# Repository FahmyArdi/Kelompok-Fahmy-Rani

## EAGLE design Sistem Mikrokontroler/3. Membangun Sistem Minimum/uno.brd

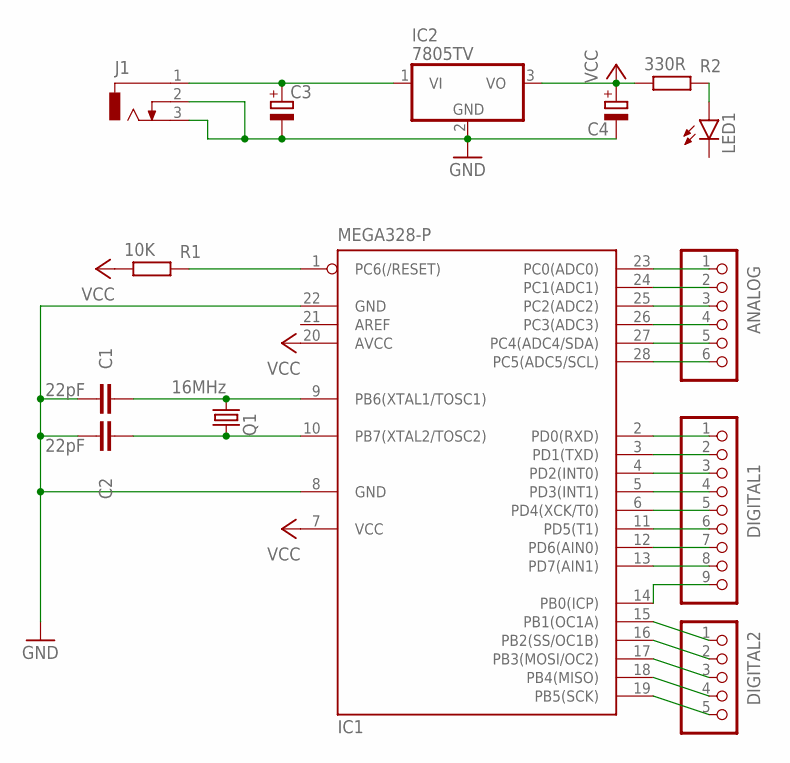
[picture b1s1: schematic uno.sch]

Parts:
ANALOG: PINHD-1X6; 1X06
C1, C2: 22pF; C025-024X044
C3, C4: CPOL-EUE2.5-6; E2,5-6
DIGITAL1: PINHD-1X9; 1X09
DIGITAL2: PINHD-1X5; 1X05
IC1: MEGA328-P; DIL28-3
IC2: 7805TV; TO220V
J1: DCJ0303
LED1: LED3MM
Q1: 16MHz; HC49U70
R1: 10K; 0207/10
R2: 330R; 0207/10

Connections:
GND: C1.1, C2.1, C3.-, C4.-, IC1.8 (GND), IC1.22 (GND), IC2.2 (GND), J1.2, J1.3
unnamed: IC1.1 (PC6(/RESET)), R1.2
unnamed: C1.2, IC1.9 (PB6(XTAL1/TOSC1)), Q1.2
unnamed: C2.2, IC1.10 (PB7(XTAL2/TOSC2)), Q1.1
unnamed: ANALOG.1, IC1.23 (PC0(ADC0))
unnamed: ANALOG.2, IC1.24 (PC1(ADC1))
unnamed: ANALOG.3, IC1.25 (PC2(ADC2))
unnamed: ANALOG.4, IC1.26 (PC3(ADC3))
unnamed: ANALOG.5, IC1.27 (PC4(ADC4/SDA))
unnamed: ANALOG.6, IC1.28 (PC5(ADC5/SCL))
unnamed: DIGITAL1.1, IC1.2 (PD0(RXD))
unnamed: DIGITAL1.2, IC1.3 (PD1(TXD))
unnamed: DIGITAL1.3, IC1.4 (PD2(INT0))
unnamed: DIGITAL1.4, IC1.5 (PD3(INT1))
unnamed: DIGITAL1.5, IC1.6 (PD4(XCK/T0))
unnamed: DIGITAL1.6, IC1.11 (PD5(T1))
unnamed: DIGITAL1.7, IC1.12 (PD6(AIN0))
unnamed: DIGITAL1.8, IC1.13 (PD7(AIN1))
unnamed: DIGITAL1.9, IC1.14 (PB0(ICP))
unnamed: DIGITAL2.1, IC1.15 (PB1(OC1A))
unnamed: DIGITAL2.2, IC1.16 (PB2(SS/OC1B))
unnamed: DIGITAL2.3, IC1.17 (PB3(MOSI/OC2))
unnamed: DIGITAL2.4, IC1.18 (PB4(MISO))
unnamed: DIGITAL2.5, IC1.19 (PB5(SCK))
unnamed: C3.+, IC2.1 (VI), J1.1
unnamed: LED1.A, R2.2
VCC: C4.+, IC1.7 (VCC), IC1.20 (AVCC), IC2.3 (VO), R1.1, R2.1

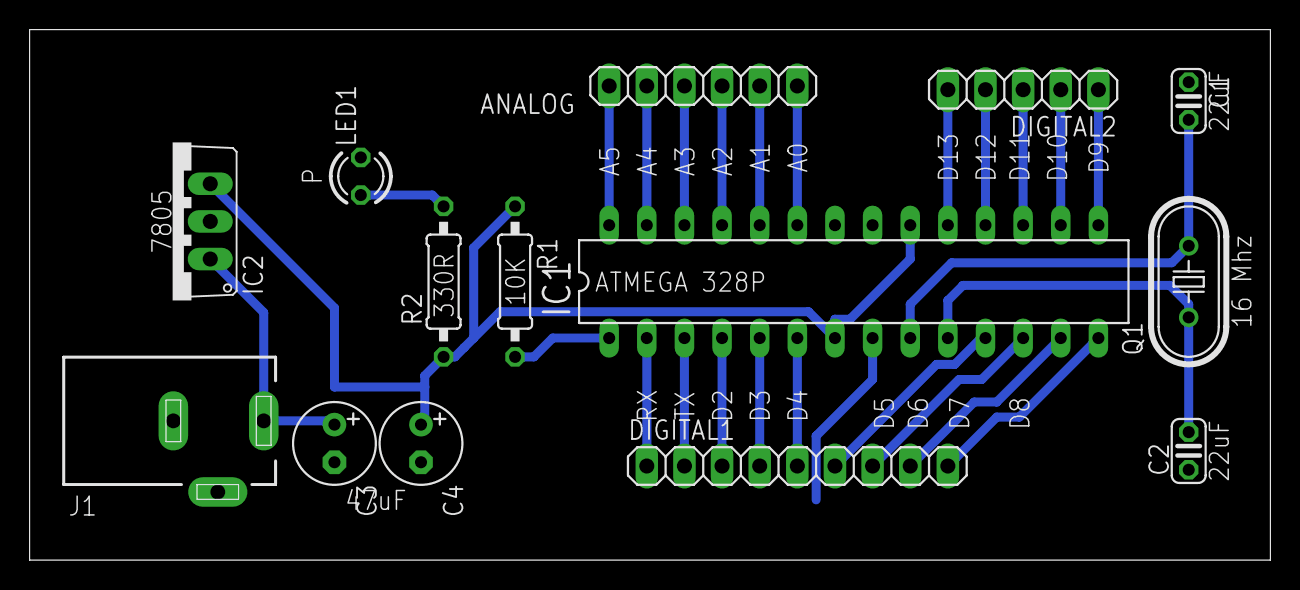
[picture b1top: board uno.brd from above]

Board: 2 copper layers, 83.7 x 35.8 mm, 14 parts (0 on the bottom side), 27 nets.

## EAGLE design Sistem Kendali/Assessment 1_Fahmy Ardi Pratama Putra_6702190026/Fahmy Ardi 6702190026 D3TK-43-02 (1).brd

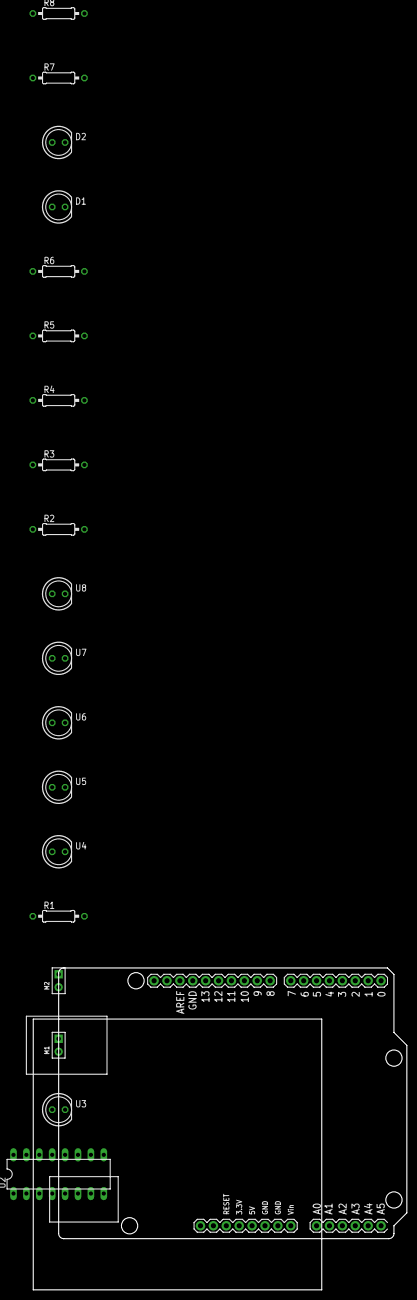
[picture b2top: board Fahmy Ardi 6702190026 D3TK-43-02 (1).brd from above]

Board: 2 copper layers, 73.6 x 63.4 mm, 20 parts (0 on the bottom side), 22 nets, no tracks yet.

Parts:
D1, D2: LED5MM
M1, M2: 2P-2.54-65/35MIL
R1, R2, R3, R4, R5, R6: 33k‎Ω; 0207/10
R7, R8: 330k‎Ω; 0207/10
U1: ARDUINO_UNO
U2: DIL16
U3, U4, U5, U6, U7, U8: LED5MM

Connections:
unnamed: R1.2, U1.A0, U3.A
unnamed: R2.2, U1.A1, U4.A
unnamed: R3.2, U1.A2, U5.A
unnamed: R4.2, U1.A3, U6.A
unnamed: R5.2, U1.A4, U7.A
unnamed: R6.2, U1.A5, U8.A
unnamed: D1.A, R7.1
unnamed: D2.K, R1.1, R2.1, R3.1, R4.1, R5.1, R6.1, U1.GND., U2.4, U2.5, U2.12, U2.13
unnamed: D2.A, R8.1
unnamed: R8.2, U1.8
unnamed: R7.2, U1.7
unnamed: U1.4, U2.1
unnamed: U1.5, U2.2
unnamed: M1.2, U2.3
unnamed: M1.1, U2.6
unnamed: U1.6, U2.7
unnamed: U1.2, U2.9
unnamed: U1.3, U2.10
unnamed: M2.2, U2.11
unnamed: M2.1, U2.14
unnamed: U1.11, U2.15
unnamed: D1.K, U1.5V, U2.8, U2.16, U4.K, U5.K, U6.K, U7.K, U8.K

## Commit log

2021-03-09 tugas sebelumnya
2021-03-10 modul 3
2021-03-22 Assigment 1 Modul 4.rar
2021-03-24 Tugas 6
2021-03-29 Assesment 1 Fahmy
2021-03-29 assessment 1 rani deliana
2021-04-01 Kasus P dan D
2021-04-14 Praktikum Mandiri
2021-04-30 Tugas Praktikum
2021-04-30 Edit
2021-05-01 edit lagi
2021-05-01 merapikan file
2021-05-01 Update File
